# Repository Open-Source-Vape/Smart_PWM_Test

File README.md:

/*
 * Components used:
 * https://www.adafruit.com/products/931
 * https://www.sparkfun.com/products/9028
 * https://www.sparkfun.com/products/8374
 * https://www.sparkfun.com/products/13760
 * https://www.sparkfun.com/products/97
 * http://www.infineon.com/cms/en/product/power/power-mosfet/20v-300v-n-channel-power-mosfet/20v-30v-n-channel-power-mosfet/IRLS3813/productType.html?productType=5546d462533600a401533d4c1e1f77fa
 * https://www.radioshack.com/products/radioshack-220-ohm-1-4w-5-carbon-film-resistor-pk-5
 * place 220 ohm resistor between MCU pin 7 and gate on mosfet 
 */

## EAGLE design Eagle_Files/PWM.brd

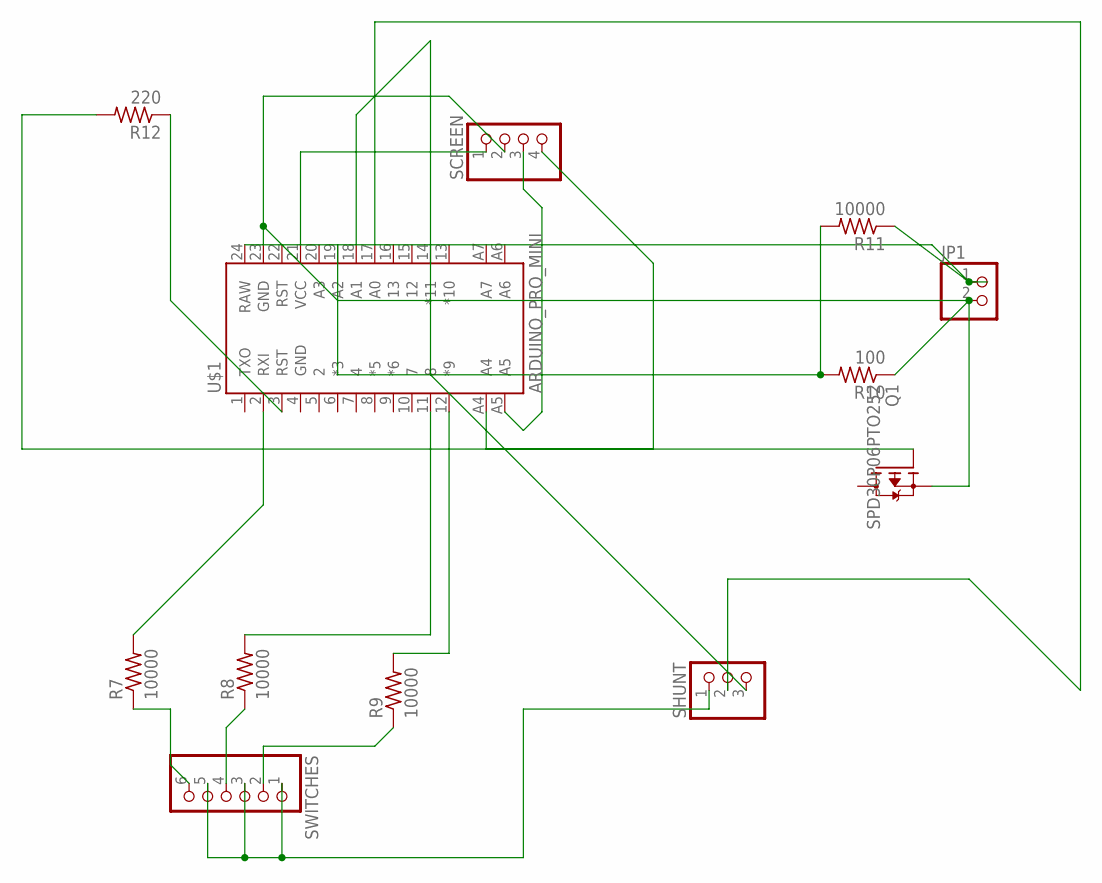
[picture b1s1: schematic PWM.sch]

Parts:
JP1: PINHD-1X2; 1X02
Q1: SPD30P06PTO252; TO252
R7, R8, R9, R11: 10000; 0204/7
R10: 100; 0204/7
R12: 220; 0204/7
SCREEN: PINHD-1X4; 1X04
SHUNT: PINHD-1X3; 1X03
SWITCHES: PINHD-1X6; 1X06
U$1: ARDUINO_PRO_MINI

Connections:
2: R7.1, R7.2, SWITCHES.6, U$1.2 (RXI)
3: R12.1, U$1.3 (RST)
11: R8.1, SWITCHES.4
12: R9.1, SWITCHES.2
19: R10.2, R11.2, U$1.19 (A2)
A0: SHUNT.2, U$1.17 (A0)
A1: SHUNT.3, U$1.18 (A1)
A4: SCREEN.4, U$1.A4
A5: SCREEN.3, U$1.A5
FET: Q1.1 (G), R12.2
GND: JP1.2, Q1.2 (S), R10.1, SCREEN.2, SHUNT.1, SWITCHES.1, SWITCHES.3, SWITCHES.5, U$1.23 (GND)
unnamed: R9.2, U$1.12 (*9)
unnamed: R8.2, U$1.11 (8)
RAW: JP1.1, R11.1, U$1.24 (RAW)
VCC: SCREEN.1, U$1.21 (VCC)

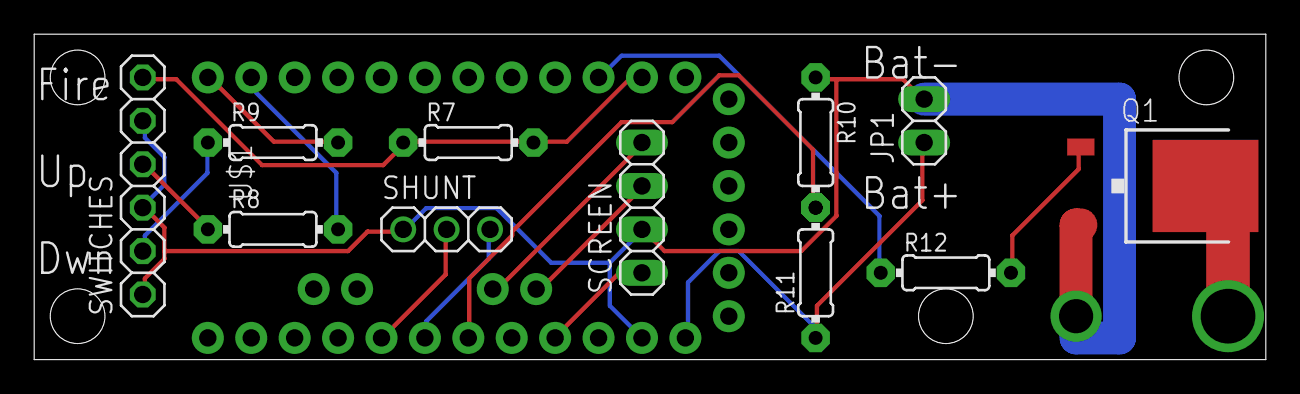
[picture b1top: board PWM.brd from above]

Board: 2 copper layers, 72.1 x 19.0 mm, 12 parts (0 on the bottom side), 15 nets.

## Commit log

2016-09-11 initial commit of pwm code with screen printout of information
2016-09-11 add todo memo
2016-09-11 add note about display source
2016-09-11 Add code for 90a INA-169 breaktout to read current on fire
2016-09-11 include EEPROM header
2016-09-11 fix eeprom header
2016-09-11 add some notation
2016-09-11 Change wording of eeprom read function to better name its purpose
2016-09-11 Update some notes again
2016-09-11 add actual output for pwm pin
2016-09-11 update Todo
2016-09-11 add more information about current reader
2016-09-11 add quick math for resistance
2016-09-11 Update a println to a print char for VFinal and insert print for Rfinal
2016-09-11 Adding some notes about how wattage detection will be implimented
2016-09-11 add quick n dirty wattage math
2016-09-11 rename high voltage to normal voltage operation
2016-09-11 rename power saving mode to a better name
2016-09-11 move quick check of voltage/current/resistance/wattage to occur only during firing
2016-09-11 add a pulsecheck to run before each fire just an idea for now
2016-09-11 disable eeprom writing of misc current calc bits
2016-09-11 Make check during pulse more realistic resistance value to look for
2016-09-11 turn off the pulse signal to ccheck resistance
2016-09-11 add 2 microsecond tick before continuing to check the resistance of the pulse
2016-09-11 hard code battery mode until sensing code is in place
2016-09-15 Trying to get LCD working layout is confusing but it prints information that is relative
2016-09-15 add note about vout
2016-09-15 change output to digitalpwm instead of analog on suggestion of mark mathis
2016-09-17 Not sure if I will stick with this core code or not
2016-09-19 small overhaul.... replace analog write with pwm library and get PWM at 100k hz as to not be audible when switching.. (not sure of efficiency dont own a scope)
2016-09-19 update hz to 490
2016-09-19 add proper VFinal / IFinal Values for real world application
2016-09-19 drop delay timer down for coil check a hair it seems to not need to fire very long at all to check if there is a coil with a 2s or greater supplying power
2016-09-19 add another level of logic to tell when pulse has been ran so it is not ran every time fire is pressed
2016-09-19 added more stuff... duty cycle display....
2016-09-19 i fell asleep before I made this commit and forgot what it is... TLDR Ill update later
2016-09-19 add updown logic for wattage
2016-09-19 add updown logic impliment wattage logic (not really active for now it just prints information doesnt use it. Change screen states to show live output vs user selected while firing and other stuff i 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
2016-09-28 complete rewrite
2016-09-28 overhaul
2016-09-28 VW mode working thanks for the math @markmatthis
2016-09-28 sanity check
2016-09-28 remove WFinal its useless since Wattage is handled by WUser
2016-09-28 Change Vout to Current Unloaded battery status
2016-09-28 update some screen layout
2016-09-28 add shitty battery thing
2016-09-28 update components used
2016-09-28 add Readme file
2016-09-28 change freq back to 20khz... intend to make this an editable item in the future
2016-09-29 changed constrain logic for duty cycle limit
2016-09-29 man i suck at fritzing
2016-09-30 pretty up display a bit
2016-09-30 add switch case array for battery charge level states
2016-09-30 finish battery array
2016-09-30 redoing defines
2016-10-01 switch back because not using button lib
2016-10-01 remove button header
2016-10-02 improve resistance check logic and change wattage levels to a more realistic output for a 2s setup
2016-10-02 fixup screen
2016-10-02 start staging multiple input range sensing
2016-10-02 fix up/down logic
2016-10-02 fix longpress logic
2016-10-02 add longpress logic for wattage up
2016-10-02 fixup some debug stuff i was doing
2016-10-02 add longpress logic for down button
2016-10-02 refine longpress logic
2016-10-02 change longpress multiplier for number added to wattage
2016-10-02 staging lock code
2016-10-02 finsh up locking logic
2016-10-02 rectify lock logic
2016-10-02 autoformat
2016-10-03 fixing everything
2016-10-16 been a while since internet no idea what i broke since last commit
2016-10-18 sleep/locking working
2016-10-23 move some things for sanity
2016-10-23 fuckup
2016-10-25 Change interrupts and add eeprom read/write of wattage
2016-10-25 fixup eeprom logic so it doesnt rape boards
2016-11-09 remove unneeded headers
2016-11-10 add max wattage error
2016-11-10 finish up wattage warnings and add a submenu for frequency editing
2016-11-10 add placeholder for menu and submenus
2016-11-10 setting locked message
2016-11-11 fixup battery checking logic
2016-11-17 add some eeprom storage for battery check on boot
2016-11-17 start staging over to ug8
2016-11-20 start staging menu for user to edit the frequency the PWM oscillates at
2016-11-20 finish staging some of the stuff for frequency editing
2016-11-20 add logic check to avoid user setting to high of freq or too low
2016-11-20 fixup menu logic a tad more
2016-11-20 frequency interaction menu is working now to set EEprom read/write of freq
2016-11-20 fix max/min logic on frequency menu
2016-11-20 add eeprom storage of frequency selected by user
2016-11-20 cherpumple
2016-11-20 add prelim eagle files for backpack PCB
2017-08-30 Update NewPWM.ino
    Add comments
2017-09-11 Add fixes for teensy compile.. gunna try ARM hardware instead
2020-01-22 include the PWM library so folks can compile this

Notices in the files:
parts and their libraries:
SparkFun-Boards: Licensing: Creative Commons ShareAlike 4.0 International - https://creativecommons.org/licenses/by-sa/4.0
